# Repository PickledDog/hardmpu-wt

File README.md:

# hardmpu-wt
 HardMPU with wavetable module support

## Overview
This is a clone of ab0tj's HardMPU board. I wanted one with a "Wave Blaster" header, so... here it is! If you don't need to install a wavetable module on your HardMPU, rather use ab0tj's original board. In particular, to quote the HardMPU repo, `the circuit design is free for non-commercial use.` The presence of this implementation does not permit commercial exploitation. If you build this, you may do so only for your own personal use. All [software](https://github.com/ab0tj/HardMPU/) is bound by the terms of the GPL. 

## Initial setup
The ATmega needs to be programmed before use. This can be done using any AVR programmer (AVRISP, STK500, USBtinyISP, USBasp etc), or a universal programmer (TL866, T48).

### Using an AVR programmer
This method programs the ATmega chip in-place (with the board fully assembled), through the J4 ISP connector. The listed programmers work similarly, but AVRDUDE will need to be told what programmer you are using. This example uses the [programmer from Pololu](https://www.pololu.com/product/3172).

Program the board loose (not plugged into a computer!) with the programmer configured to power the target at 5V. The required firmware can be found [in ab0tj's repository](https://github.com/ab0tj/HardMPU/tree/master/bin) (download all files), and [AVRDUDE](https://github.com/avrdudes/avrdude/) is used to install the firmware onto the ATmega.

You will need to modify the `program.bat` to reflect your programmer and environment. For example, to use a Pololu programmer detected at COM4, change (per-line):
```
-c usbasp-clone
```
to
```
-c stk500v2 -P COM4
```
For Mac and Linux, change the BATch file to a shell script and adapt it accordingly (use `/dev/ttyUSB0` instead of `COM4` etc).

### Using a TL866
If you're using a TL866 or T48, the firmware is programmed directly to the ATmega chip before installing it - the J4 connector isn't used here, and can be omitted. Download `HardMPU.hex` from [ab0tj's repository](https://github.com/ab0tj/HardMPU/tree/master/bin) and open it with the standard XGpro tool. Go to the **Config** tab and set the fuses as follows:

With the firmware loaded and the fuses set, go ahead and program the ATmega chip.

## User port
The optional User port (J2) allows adventurous builders to add features to the board, either internally or externally. It breaks out 4 GPIO pins, an I²C interface, the "Internal" serial interface (shared with the Wavetable header), and fused power and ground pins. Either regular or right-angled header (as pictured) can be installed in the J2 position; a hole will need to be cut in the bracket for external access. You will need to write your own code to use these interfaces - maybe add a status display using a common I²C LCD? The possibilities are not particularly limited!

## Usage
With the card built and the chip programmed, it's ready to be installed in the ISA slot of your vintage PC. Copy `hardmpu.com` from the firmware folder above to the PC's hard drive - this is the config tool for HardMPU. Use it to select between internal and external MIDI devices, enable a delay for "rev 0" Roland MT-32s, and other miscellaneous options. Settings *do not persist* across reboots, so this will need to be added to `autoexec.bat` if the defaults aren't adequate.

### External MIDI
To connect it to an external synthesizer, you'll need a "Sound Blaster MIDI" cable - you can find a used one, [buy a new one](https://www.ebay.com/sch/i.html?_nkw=game+port+midi+cable), or [build your own](https://github.com/PickledDog/sb-midi). If shopping for a new one, *make sure to pick the one with large black DA-15 plugs* since it has the electronics in the plug. ***Do not use the "metal plugs" kind, they are passive and may damage your synthesizer.***

### Internal MIDI ("Wave Blaster")
Plug the wavetable board onto the 26-pin header, aligning the pin 1 arrows on both boards. Audio is output through both the 3.5mm jack and the AuxOut header on the board. The latter can be fed into your regular sound card using a standard "MPC2" CD Audio cable (assuming it has a spare input). You will need to use the `hardmpu.com` tool to select the internal MIDI port.

## Part selection
The design permits "nicer" parts than necessary - for example, the audio jack footprint accepts both switched and unswitched sockets. Not all pads and holes in the board need to be filled. The OPA2134 can be substituted for other common dual opamps (like the NE5532). Some connectors are optional - J2 and J5 in particular are seldom-used. An [ATmega1284](https://www.mouser.com/ProductDetail/556-ATMEGA1284-PU) can be used in place of the ATmega1284P if the latter isn't in stock; you will need to update `program.bat` accordingly.

## Parts list
Bill Of Materials and part references are below. The specified parts are just the ones I used, and can be substituted as needed - Mouser links provided for convenience and reference. You will need to drill a single hole in the specified bracket for the audio jack - refer to the PCB file for size and location.

| Reference | Value | Qty | Mouser link |
| --------- | ----- | --- | ----------- |
| C1-C10 | 0.1uF ceramic | 10 | [KEMET C315C104M5U5TA](https://www.mouser.com/ProductDetail/80-C315C104M5U-TR) |
| C11, C12 | 22pF ceramic | 2 | [KEMET C315C220K2G5TA](https://www.mouser.com/ProductDetail/80-C315C220K2G) |
| C13, C14 | 0.47uF ceramic | 2 | [TDK FG18X7R1H474K](https://www.mouser.com/ProductDetail/810-FG18X7R1H474KRT0) |
| C15, C16 | 1uF ceramic | 2 | [TDK FG18X7R1E105K](https://www.mouser.com/ProductDetail/810-FG18X7R1E105KRT0) |
| C17 | 22μF electrolytic | 1 | [Panasonic ECE-A1AKS220](https://www.mouser.com/ProductDetail/667-ECE-A1AKS220) |
| F1 | 500mA PPTC fuse | 1 | [Bourns MF-R050-0-17](https://www.mouser.com/ProductDetail/652-MF-R050-0-17) |
| J1 | D-Sub DA-15 female | 1 | [Amphenol L77SDA15SA4CH4F](https://www.mouser.com/ProductDetail/523-L77SDA15SA4CH4F) |
| J2 | 2x5 right-angle header | 1 | [Amphenol 10129382-910002BLF](https://www.mouser.com/ProductDetail/649-1012938291002BLF) |
| J3 | 3.5mm jack socket | 1 | [CUI SJ1-3553NG](https://www.mouser.com/ProductDetail/490-SJ1-3553NG) |
| J4 | 2x3 box header | 1 | [Wurth 61200621621](https://www.mouser.com/ProductDetail/710-61200621621) |
| J5 | 2x5 box header | 1 | [Wurth 61201021621](https://www.mouser.com/ProductDetail/710-61201021621) |
| J6 | 2x13 header | 1 | [Amphenol 67997-226HLF](https://www.mouser.com/ProductDetail/649-67997-226HLF) |
| J7 | CD-Audio socket | 1 | [Molex 70551-0003](https://www.mouser.com/ProductDetail/538-70551-0003) |
| JP1 | 2x4 header | 1 | [Amphenol 10129381-908002BLF](https://www.mouser.com/ProductDetail/649-1012938190802BLF) |
| JP2 | 2x6 header | 1 | [Amphenol 10129381-912002BLF](https://www.mouser.com/ProductDetail/649-1012938191202BLF) |
| JP3 | 2x3 header | 1 | [Amphenol 10129381-906002BLF](https://www.mouser.com/ProductDetail/649-1012938190602BLF) |
| | jumpers | 4 | [Harwin M7583-46](https://www.mouser.com/ProductDetail/855-M7583-46)
| R1-R3 | 4k7Ω resistor | 3 | [Yageo CFR-25JR-52-4K7](https://www.mouser.com/ProductDetail/603-CFR-25JR-524K7) |
| R4, R5 | 220Ω resistor | 2 | [Yageo CFR-25JR-52-220R](https://www.mouser.com/ProductDetail/603-CFR-25JR-52220R) |
| U1, U2 | 74HCT138 | 2 | [TI CD74HCT138E](https://www.mouser.com/ProductDetail/595-CD74HCT138E) |
| U3 | 74HCT08 | 1 | [TI CD74HCT08E](https://www.mouser.com/ProductDetail/595-CD74HCT08E) |
| U4, U5 | 74HCT574 | 2 | [TI CD74HCT574E](https://www.mouser.com/ProductDetail/595-CD74HCT574E) |
| U6 | 74HCT240 | 1 | [TI SN74HCT240N](https://www.mouser.com/ProductDetail/595-SN74HCT240N) |
| U7, U8 | 74HCT74 | 2 | [TI CD74HCT74E](https://www.mouser.com/ProductDetail/595-CD74HCT74E) |
| U9 | ATmega1284P | 1 | [Atmel ATmega1284P](https://www.mouser.com/ProductDetail/556-ATMEGA1284P-PU) |
| | socket | 1 | [Amphenol DILB40P-223TLF](https://www.mouser.com/ProductDetail/649-DILB40P223TLF) |
| U10 | 78L05 | 1 | [ST L78L05ACZ](https://www.mouser.com/ProductDetail/511-L78L05ACZ) |
| U11 | 79L05 | 1 | [ST L79L05ACZ](https://www.mouser.com/ProductDetail/511-L79L05ACZ) |
| U12 | OPA2134 | 1 | [TI OPA2134PA](https://www.mouser.com/ProductDetail/595-OPA2134PA) |
| Y1 | 20MHz crystal | 1 | [Arbacon ABL-20.000MHz-B1U](https://www.mouser.com/ProductDetail/815-ABL-20-B1U) |
| bracket | ISA DA-15 bracket | 1 | [Keystone 9200-11](https://www.mouser.com/ProductDetail/534-9200-11) |

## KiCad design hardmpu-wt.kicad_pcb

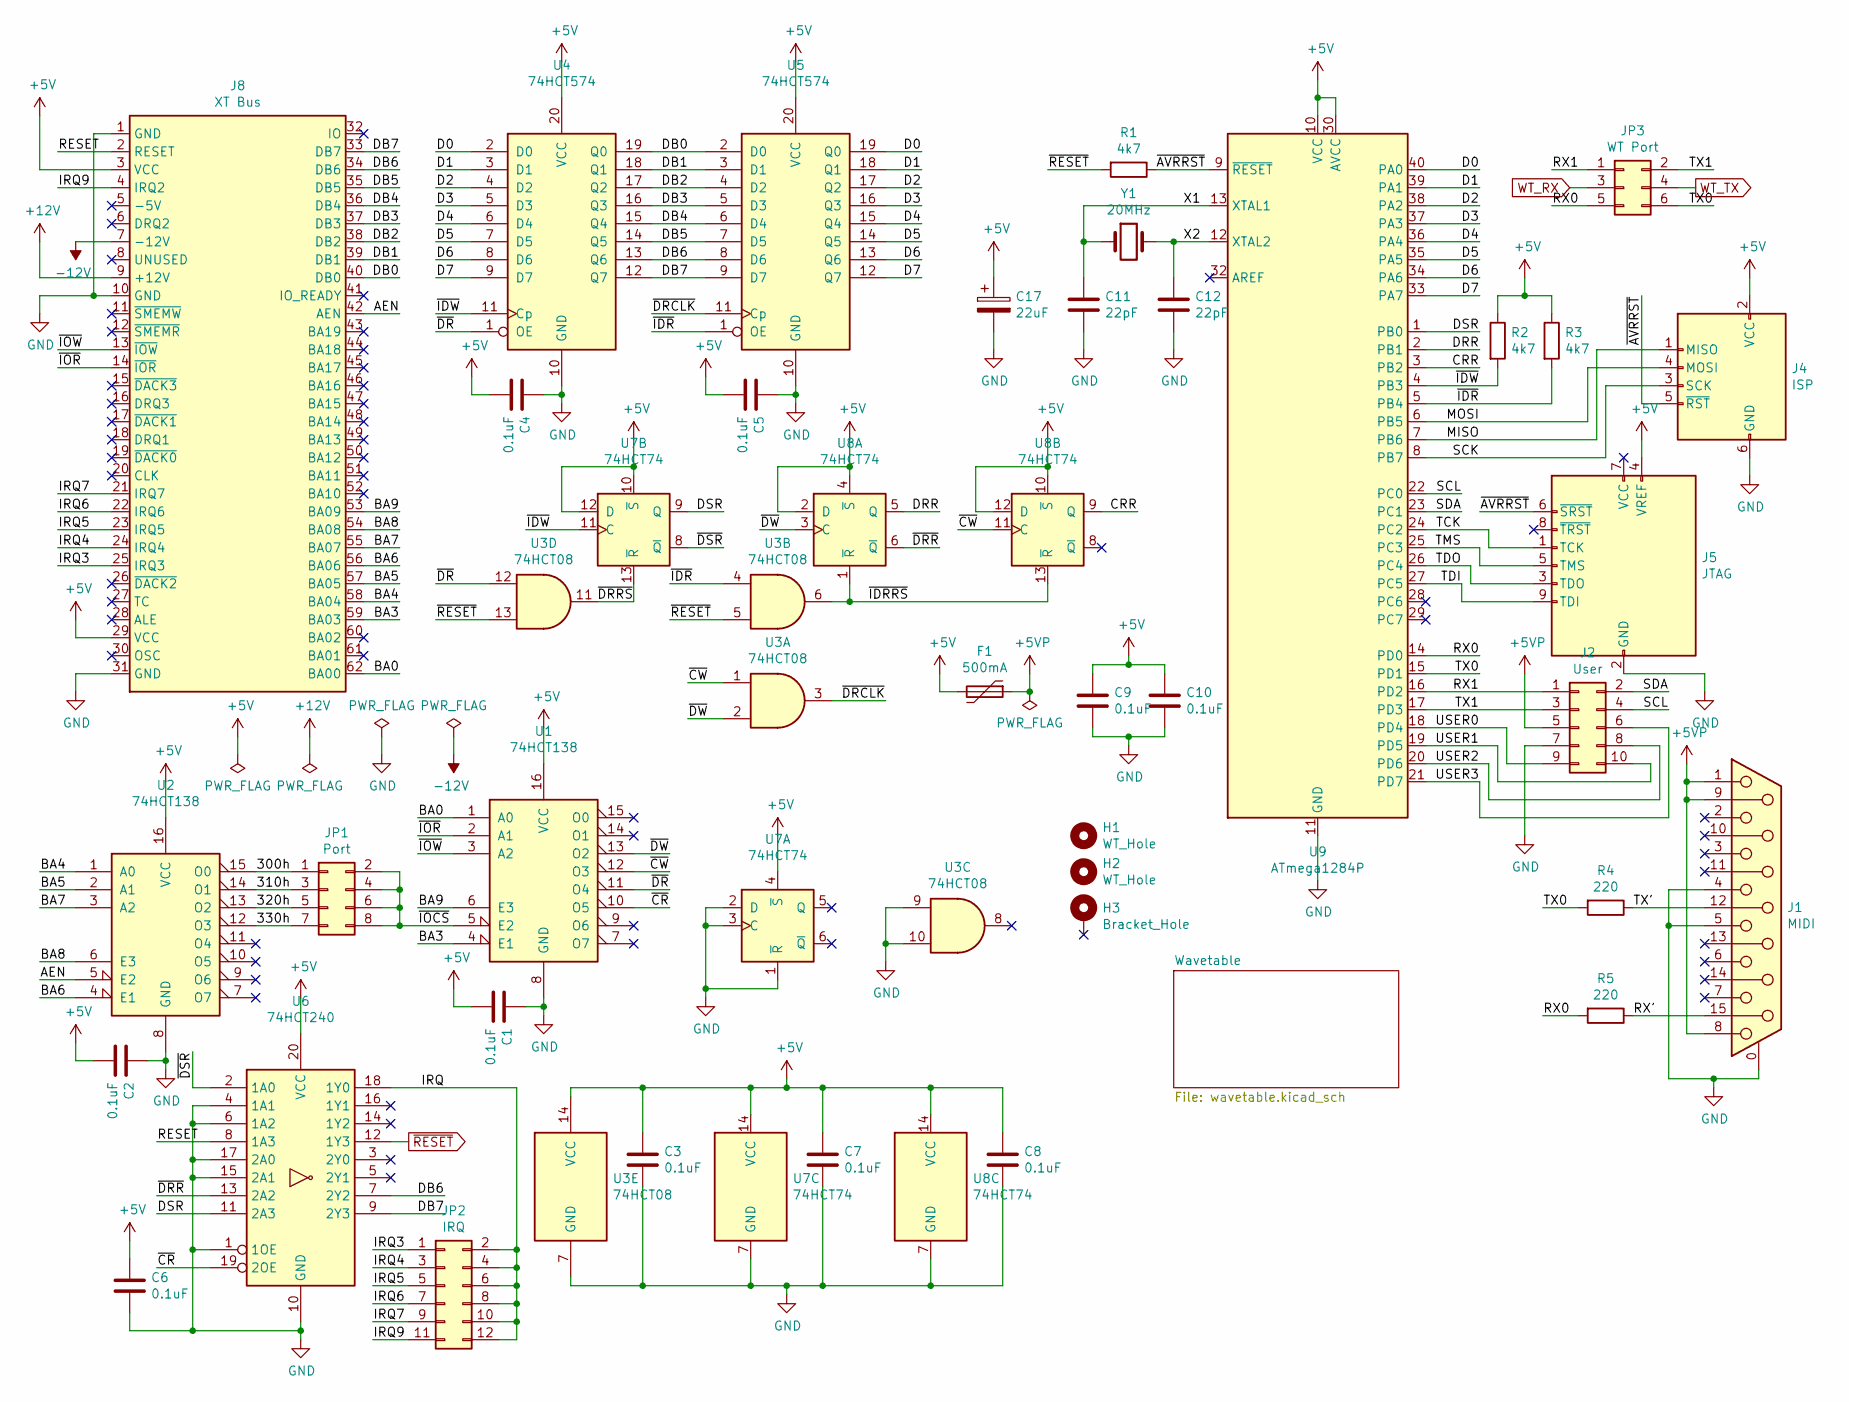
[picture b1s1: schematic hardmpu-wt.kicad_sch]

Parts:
C1, C2, C3, C4, C5, C6, C7, C8, C9, C10: 0.1uF; C_Disc_D3.0mm_W1.6mm_P2.50mm
C11, C12: 22pF; C_Disc_D3.0mm_W1.6mm_P2.50mm
C17: 22uF; CP_Radial_D5.0mm_P2.00mm
F1: 500mA; Fuse_BelFuse_0ZRE0005FF_L8.3mm_W3.8mm
H1, H2: WT_Hole; MountingHole_3.2mm_M3
H3: Bracket_Hole; MountingHole_3.2mm_M3_Pad
J1: MIDI; DSUB-15_Female_Horizontal_P2.77x2.84mm_EdgePinOffset7.70mm_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
J2: User; PinHeader_2x05_P2.54mm_Horizontal
J4: ISP; IDC-Header_2x03_P2.54mm_Vertical
J5: JTAG; IDC-Header_2x05_P2.54mm_Vertical
J8: XT Bus; BUS_XT
JP1: Port; PinHeader_2x04_P2.54mm_Vertical
JP2: IRQ; PinHeader_2x06_P2.54mm_Vertical
JP3: WT Port; PinHeader_2x03_P2.54mm_Vertical
R1, R2, R3: 4k7; R_Axial_DIN0207_L6.3mm_D2.5mm_P7.62mm_Horizontal
R4, R5: 220; R_Axial_DIN0207_L6.3mm_D2.5mm_P7.62mm_Horizontal
U1, U2: 74HCT138; DIP-16_W7.62mm_LongPads
U3: 74HCT08; DIP-14_W7.62mm_LongPads
U4, U5: 74HCT574; DIP-20_W7.62mm_LongPads
U6: 74HCT240; DIP-20_W7.62mm_LongPads
U7, U8: 74HCT74; DIP-14_W7.62mm_LongPads
U9: ATmega1284P; DIP-40_W15.24mm_LongPads
Y1: 20MHz; Crystal_HC49-4H_Vertical

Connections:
+5V: C1.2, C2.2, C3.1, C4.2, C5.2, C6.1, C7.1, C8.1, C9.1, C10.1, C17.1, F1.2, J4.2 (VCC), J5.4 (VREF), J8.3 (VCC), J8.29 (VCC), R2.1, R3.1, U1.16 (VCC), U2.16 (VCC), U3.14 (VCC), U4.20 (VCC), U5.20 (VCC), U6.20 (VCC), U7.4 (~S), U7.10 (~S), U7.12 (D), U7.14 (VCC), U8.2 (D), U8.4 (~S), U8.10 (~S), U8.12 (D), U8.14 (VCC), U9.10 (VCC), U9.30 (AVCC); also elsewhere on the board
+5VP: F1.1, J1.1, J1.8, J1.9, J2.5
+12V: J8.9 (+12V); also elsewhere on the board
-12V: J8.7 (-12V); also elsewhere on the board
/300h: JP1.1, U2.15 (O0)
/310h: JP1.3, U2.14 (O1)
/320h: JP1.5, U2.13 (O2)
/330h: JP1.7, U2.12 (O3)
/AEN: J8.42 (AEN), U2.5 (E2)
/BA0: J8.62 (BA00), U1.1 (A0)
/BA3: J8.59 (BA03), U1.4 (E1)
/BA4: J8.58 (BA04), U2.1 (A0)
/BA5: J8.57 (BA05), U2.2 (A1)
/BA6: J8.56 (BA06), U2.4 (E1)
/BA7: J8.55 (BA07), U2.3 (A2)
/BA8: J8.54 (BA08), U2.6 (E3)
/BA9: J8.53 (BA09), U1.6 (E3)
/CRR: U8.9 (Q), U9.3 (PB2)
/D0: U4.2 (D0), U5.19 (Q0), U9.40 (PA0)
/D1: U4.3 (D1), U5.18 (Q1), U9.39 (PA1)
/D2: U4.4 (D2), U5.17 (Q2), U9.38 (PA2)
/D3: U4.5 (D3), U5.16 (Q3), U9.37 (PA3)
/D4: U4.6 (D4), U5.15 (Q4), U9.36 (PA4)
/D5: U4.7 (D5), U5.14 (Q5), U9.35 (PA5)
/D6: U4.8 (D6), U5.13 (Q6), U9.34 (PA6)
/D7: U4.9 (D7), U5.12 (Q7), U9.33 (PA7)
/DB0: J8.40 (DB0), U4.19 (Q0), U5.2 (D0)
/DB1: J8.39 (DB1), U4.18 (Q1), U5.3 (D1)
/DB2: J8.38 (DB2), U4.17 (Q2), U5.4 (D2)
/DB3: J8.37 (DB3), U4.16 (Q3), U5.5 (D3)
/DB4: J8.36 (DB4), U4.15 (Q4), U5.6 (D4)
/DB5: J8.35 (DB5), U4.14 (Q5), U5.7 (D5)
/DB6: J8.34 (DB6), U4.13 (Q6), U5.8 (D6), U6.7 (2Y2)
/DB7: J8.33 (DB7), U4.12 (Q7), U5.9 (D7), U6.9 (2Y3)
/DRR: U8.5 (Q), U9.2 (PB1)
/DSR: U6.11 (2A3), U7.9 (Q), U9.1 (PB0)
/IRQ: JP2.2, JP2.4, JP2.6, JP2.8, JP2.10, JP2.12, U6.18 (1Y0)
/IRQ3: J8.25 (IRQ3), JP2.1
/IRQ4: J8.24 (IRQ4), JP2.3
/IRQ5: J8.23 (IRQ5), JP2.5
/IRQ6: J8.22 (IRQ6), JP2.7
/IRQ7: J8.21 (IRQ7), JP2.9
/IRQ9: J8.4 (IRQ2), JP2.11
/MISO: J4.1 (MISO), U9.7 (PB6)
/MOSI: J4.4 (MOSI), U9.6 (PB5)
/RESET: J8.2 (RESET), U6.8 (1A3)
/RX0: JP3.5, R5.2, U9.14 (PD0)
/RX1: J2.1, JP3.1, U9.16 (PD2)
/RX': J1.15, R5.1
/SCK: J4.3 (SCK), U9.8 (PB7)
/SCL: J2.4, U9.22 (PC0)
/SDA: J2.2, U9.23 (PC1)
/TCK: J5.1 (TCK), U9.24 (PC2)
/TDI: J5.9 (TDI), U9.27 (PC5)
/TDO: J5.3 (TDO), U9.26 (PC4)
/TMS: J5.5 (TMS), U9.25 (PC3)
/TX0: JP3.6, R4.2, U9.15 (PD1)
/TX1: J2.3, JP3.2, U9.17 (PD3)
/TX': J1.12, R4.1
/USER0: J2.9, U9.18 (PD4)
/USER1: J2.10, U9.19 (PD5)
/USER2: J2.8, U9.20 (PD6)
/USER3: J2.6, U9.21 (PD7)
/X1: C11.1, U9.13 (XTAL1), Y1.1
/X2: C12.1, U9.12 (XTAL2), Y1.2
/~AVRRST: J4.5 (~RST), J5.6 (~SRST), R1.1, U9.9 (~RESET)
/~CR: U1.10 (O5), U6.19 (2OE)
/~CW: U1.12 (O3), U3.1, U8.11 (C)
/~DRCLK: U3.3, U5.11 (Cp)
/~DRRS: U3.11, U7.13 (~R)
/~DRR: U6.13 (2A2), U8.6 (~Q)
/~DR: U1.11 (O4), U3.12, U4.1 (OE)
/~DSR: U6.2 (1A0), U7.8 (~Q)
/~DW: U1.13 (O2), U3.2, U8.3 (C)
/~IDRRS: U3.6, U8.1 (~R), U8.13 (~R)
/~IDR: R3.2, U3.4, U5.1 (OE), U9.5 (PB4)
/~IDW: R2.2, U4.11 (Cp), U7.11 (C), U9.4 (PB3)
/~IOCS: JP1.2, JP1.4, JP1.6, JP1.8, U1.5 (E2)
/~IOR: J8.14 (~IOR), U1.2 (A1)
/~IOW: J8.13 (~IOW), U1.3 (A2)
GND: C1.1, C2.1, C3.2, C4.1, C5.1, C6.2, C7.2, C8.2, C9.2, C10.2, C11.2, C12.2, C17.2, J1.0 (PAD), J1.4, J1.5, J2.7, J4.6 (GND), J5.2 (GND), J5.10 (GND), J8.1 (GND), J8.10 (GND), J8.31 (GND), U1.8 (GND), U2.8 (GND), U3.7 (GND), U3.9, U3.10, U4.10 (GND), U5.10 (GND), U6.1 (1OE), U6.4 (1A1), U6.6 (1A2), U6.10 (GND), U6.15 (2A1), U6.17 (2A0), U7.1 (~R), U7.2 (D), U7.3 (C), U7.7 (GND), U8.7 (GND), U9.11 (GND), U9.31 (GND); also elsewhere on the board
WT_RX: JP3.3; also elsewhere on the board
WT_TX: JP3.4; also elsewhere on the board
~RESET: R1.2, U3.5, U3.13, U6.12 (1Y3); also elsewhere on the board

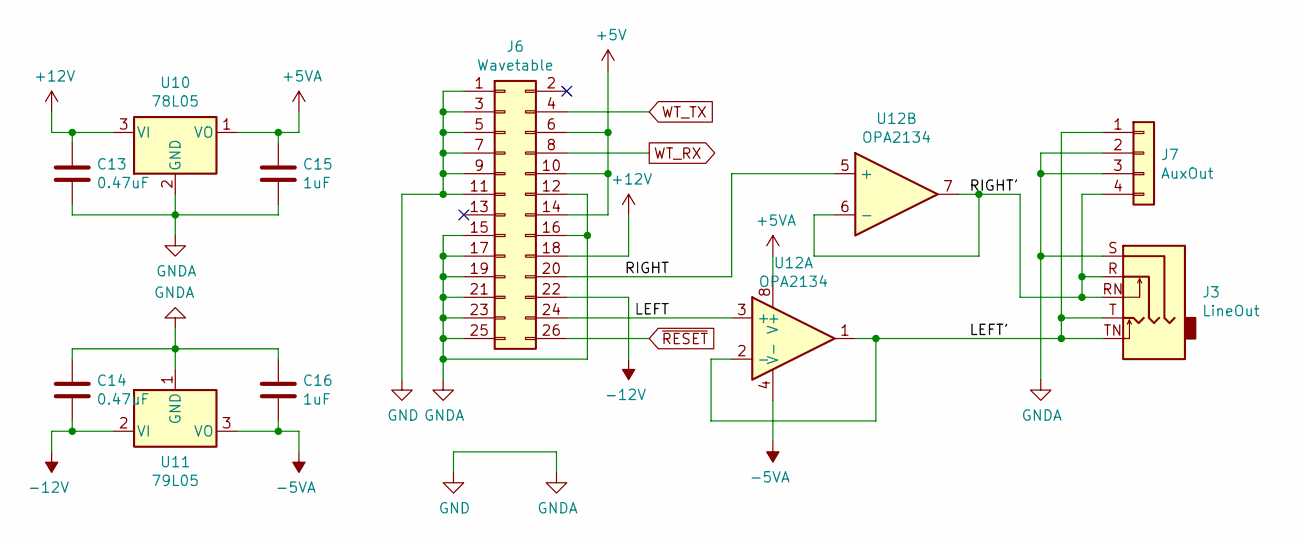
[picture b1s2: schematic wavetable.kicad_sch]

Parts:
C13, C14: 0.47uF; C_Disc_D3.0mm_W2.0mm_P2.50mm
C15, C16: 1uF; C_Disc_D3.0mm_W2.0mm_P2.50mm
J3: LineOut; Jack_3.5mm_CUI_SJ1-3555NG
J6: Wavetable; PinHeader_2x13_P2.54mm_Vertical
J7: AuxOut; Molex_SL_70551-0003_1x04_P2.54mm_Horizontal
U10: 78L05; TO-92
U11: 79L05; TO-92
U12: OPA2134; DIP-8_W7.62mm_LongPads

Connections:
+5V: J6.6, J6.10, J6.14; also elsewhere on the board
+5VA: C15.1, U10.1 (VO), U12.8 (V+)
+12V: C13.1, J6.18, U10.3 (VI); also elsewhere on the board
-5VA: C16.2, U11.3 (VO), U12.4 (V-)
-12V: C14.2, J6.22, U11.2 (VI); also elsewhere on the board
/Wavetable/LEFT: J6.24, U12.3 (+)
/Wavetable/LEFT': J3.T, J3.TN, J7.1, U12.1, U12.2 (-)
/Wavetable/RIGHT: J6.20, U12.5 (+)
/Wavetable/RIGHT': J3.R, J3.RN, J7.4, U12.6 (-), U12.7
GND: C13.2, C14.1, C15.2, C16.1, J3.S, J6.1, J6.3, J6.5, J6.7, J6.9, J6.11, J6.12, J6.15, J6.16, J6.17, J6.19, J6.21, J6.23, J6.25, J7.2, J7.3, U10.2 (GND), U11.1 (GND); also elsewhere on the board
WT_RX: J6.8; also elsewhere on the board
WT_TX: J6.4; also elsewhere on the board
~RESET: J6.26; also elsewhere on the board

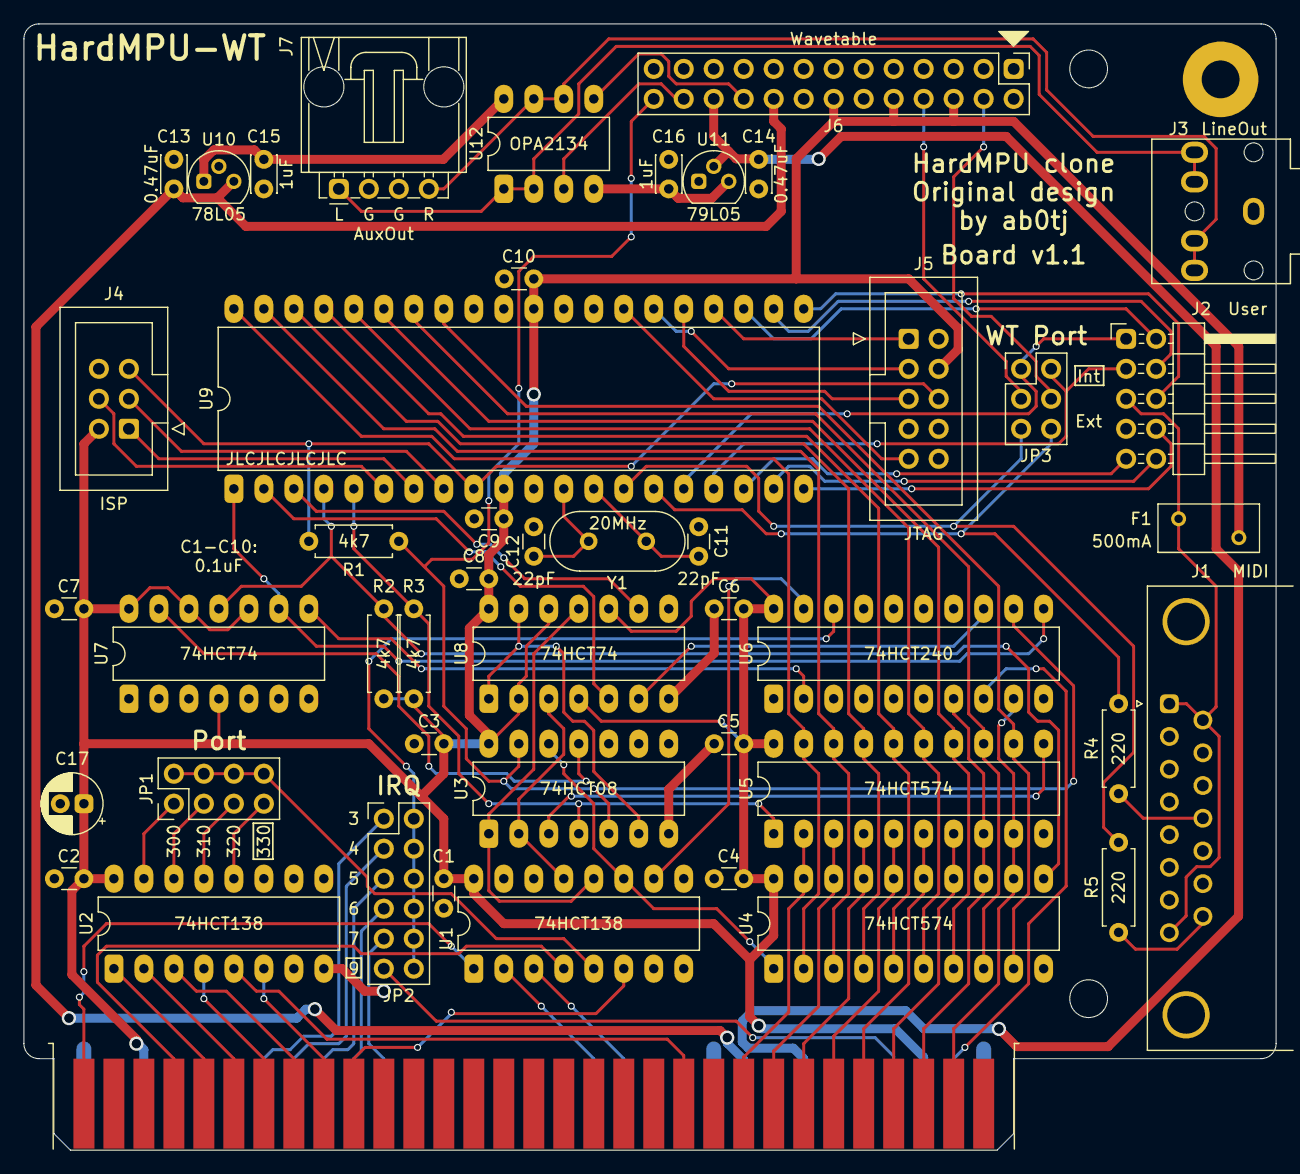
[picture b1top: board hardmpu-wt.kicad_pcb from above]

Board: 2 copper layers, 106.0 x 95.4 mm, 50 parts (0 on the bottom side), 90 nets.

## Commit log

2022-04-16 Tweak component values
2022-04-16 Initial documentation
2022-05-03 Add photo of board
2022-05-03 Add missing image
2022-05-20 Move DA-15 so board aligns with Keystone 9200-11 bracket
    Adapt board to fit common Keystone 9200-11, add jumpers to switch wavetable between Internal and External UART
2022-06-20 Update photo for board v1.1, flesh out README
2022-07-23 Update to Kicad 6, fix DRC errors
2023-01-30 Migrate project to KiCad 6
2023-07-04 Add instructions for pre-programming with a TL866
2023-07-07 Add Usage section
